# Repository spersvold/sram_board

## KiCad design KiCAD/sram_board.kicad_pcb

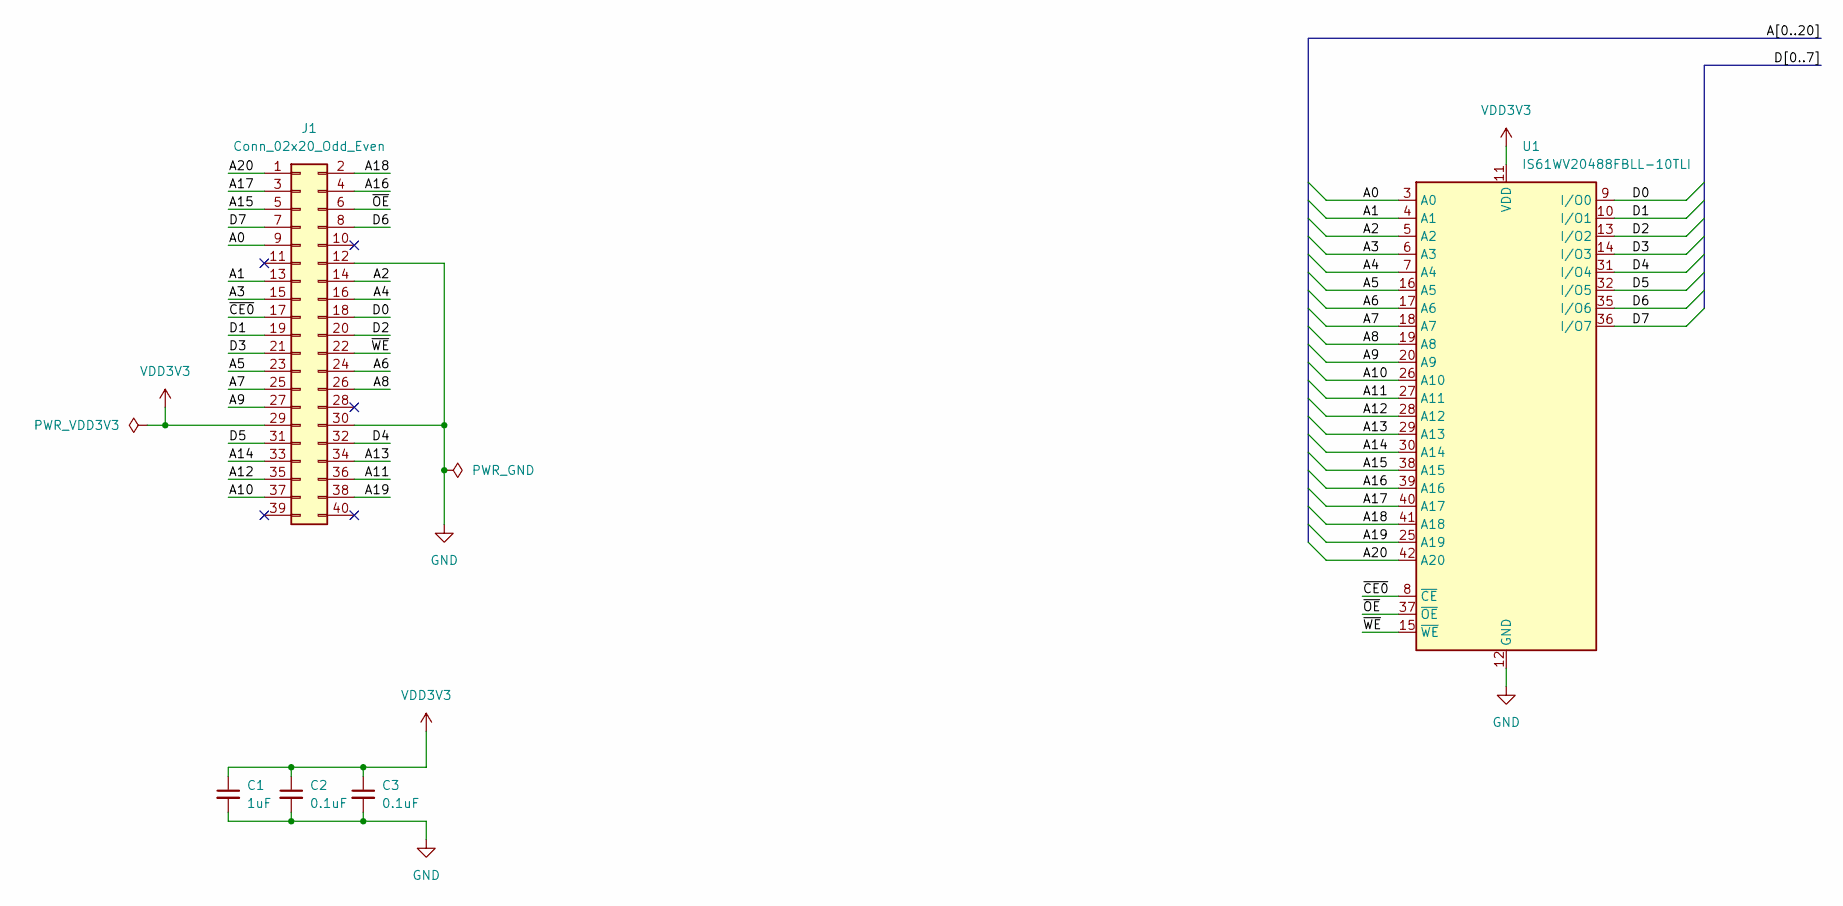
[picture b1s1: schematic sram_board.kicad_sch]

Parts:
C1: 1uF; C_0603_1608Metric
C2, C3: 0.1uF; C_0402_1005Metric
J1: Conn_02x20_Odd_Even; PinSocket_2x20_P2.54mm_Horizontal
U1: IS61WV20488FBLL-10TLI; TSOP-II-44_10.16x18.41mm_P0.8mm

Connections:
/A0: J1.9, U1.3 (A0)
/A1: J1.13, U1.4 (A1)
/A2: J1.14, U1.5 (A2)
/A3: J1.15, U1.6 (A3)
/A4: J1.16, U1.7 (A4)
/A5: J1.23, U1.16 (A5)
/A6: J1.24, U1.17 (A6)
/A7: J1.25, U1.18 (A7)
/A8: J1.26, U1.19 (A8)
/A9: J1.27, U1.20 (A9)
/A10: J1.37, U1.26 (A10)
/A11: J1.36, U1.27 (A11)
/A12: J1.35, U1.28 (A12)
/A13: J1.34, U1.29 (A13)
/A14: J1.33, U1.30 (A14)
/A15: J1.5, U1.38 (A15)
/A16: J1.4, U1.39 (A16)
/A17: J1.3, U1.40 (A17)
/A18: J1.2, U1.41 (A18)
/A19: J1.38, U1.25 (A19)
/A20: J1.1, U1.42 (A20)
/D0: J1.18, U1.9 (I/O0)
/D1: J1.19, U1.10 (I/O1)
/D2: J1.20, U1.13 (I/O2)
/D3: J1.21, U1.14 (I/O3)
/D4: J1.32, U1.31 (I/O4)
/D5: J1.31, U1.32 (I/O5)
/D6: J1.8, U1.35 (I/O6)
/D7: J1.7, U1.36 (I/O7)
/~CE0: J1.17, U1.8 (~CE)
/~OE: J1.6, U1.37 (~OE)
/~WE: J1.22, U1.15 (~WE)
GND: C1.2, C2.2, C3.2, J1.12, J1.30, U1.12 (GND), U1.34 (GND)
VDD3V3: C1.1, C2.1, C3.1, J1.29, U1.11 (VDD), U1.33 (VDD)

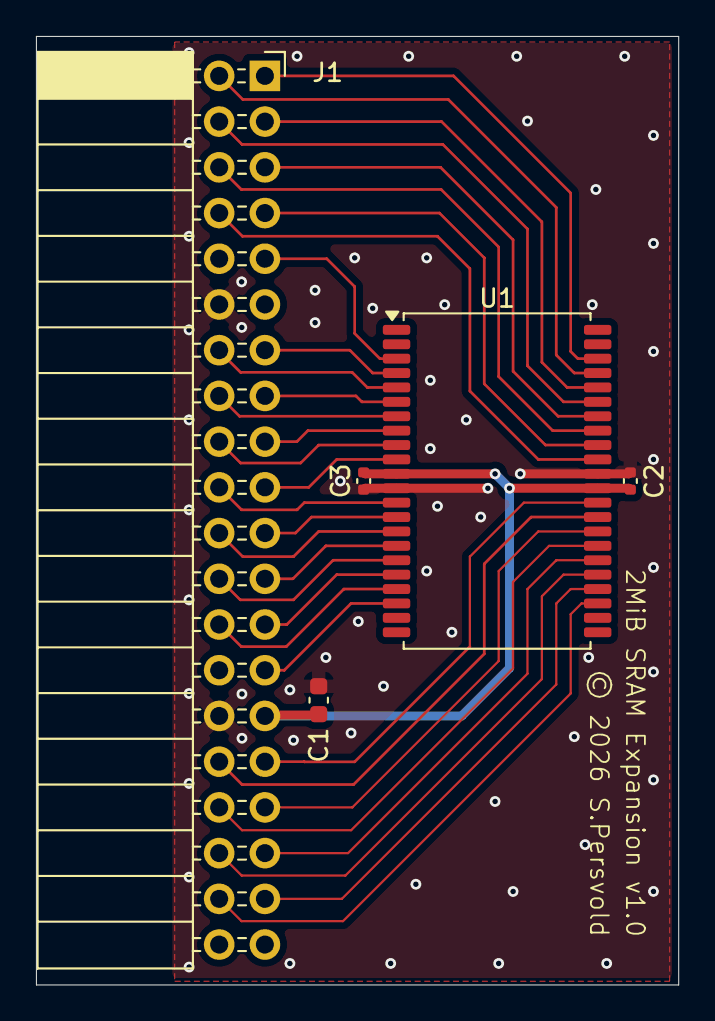
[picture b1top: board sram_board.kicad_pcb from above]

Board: 2 copper layers, 35.7 x 52.7 mm, 5 parts (0 on the bottom side), 34 nets.

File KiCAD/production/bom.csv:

Designator,Footprint,Quantity,Value,LCSC Part #
C1,0603,1,1uF,
"C2, C3",0402,2,0.1uF,
J1,PinSocket_2x20_P2.54mm_Horizontal,1,Conn_02x20_Odd_Even,
U1,TSOP-II-44_10.16x18.41mm_P0.8mm,1,IS61WV20488FBLL-10TLI,

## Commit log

2026-05-27 Add KiCAD project and symbol
2026-05-27 Add SRAM datasheet
2026-05-27 Version 1.0

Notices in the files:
KiCAD/sram_board.kicad_pcb:
© 2026 S.Persvold
